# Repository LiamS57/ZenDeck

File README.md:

# ZenDeck

<h3 align="center">
This is a hard-fork of CNCDan's fantastic ZenDeck project, which incorporates a Ryzen-powered Mini-PC into a custom-built handheld gaming console!
</h3>

## Acknowledgement

The majority of this work is based on the previous work of CNCDan (see the upstream repo!). As such, my adjustments would not have been possible without many months of development on his end. If you find that this work benefits you or inspires you to make your own ZenDeck, please take a look at his original project -- as well as his other works -- and show him your support!

**CNCDan's Youtube:**
https://www.youtube.com/@cncdan

**CNCDan's Original ZenDeck Development Log:**
https://www.youtube.com/watch?v=_ST59qbFj8Q&list=PLy9j9_dmmg2TrMOIG65j3nOELqgDXPkkn

## Info

This repository intends to serve as a build diary and general knowledge-base for my specific implementation of the ZenDeck, in the hopes that the details of my attempt are helpful to others interested in constructing one.
I had started my implementation a few months before forking the repository, so some details are not part of the commit history; however, **there is still quite a bit to finish**, and future changes/updates will be recorded here.

Please note that this is not a one-to-one recreation -- I have made several design changes to better suit my use-case. The major points are provided in this readme, but smaller changes are described in more detail in each directory.

## Features

- Customizable mounting system for other Mini-PCs
- 8" 1280x800 60hz IPS display (with touch)
- Full-sized Hall effect Joysticks
- Hall effect Triggers
- Full-sized rumble motors *[IN PROGRESS]*
- IMU/Gyroscopic aim-assist *[IN PROGRESS]*
- Custom USB HID-based controller using LUFA
- Trackpad
- Room for up to 88.8Wh battery capacity (using 6000mah 21700 cells).
- USB-C Charging, power path management and OS integration over USB for battery capacity reporting

## Major Design Changes

The following is a (non-exhaustive) list of high-level design changes I've made from the original design. For more information on smaller details changed, please see the individual section readmes and the commit log.
- Mini-PC: Beelink SER5 Max L (Ryzen 7 6800H, 32GB RAM)
- 2-microcontroller control design instead of 3
  <!-- - To conserve on cost and complexity, I have opted to remove the RHS microcontroller in favor of completely running the controller inputs off of a single Atmega32u4. This also allows me to fit all PCB uC USB connections on a single HS8836A for on-the-go reprogramability. -->
- Pure AVR C instead of Arduino.h
- Higher power BMS (19V, 5A) *[IN PROGRESS]*
- Replacement of the TRRS port with an I2C bus header

## Progress
*[COMING SOON]*

## License

This project is licensed under the **CERN Open Hardware Licence Version 2 – Strongly Reciprocal** (CERN-OHL-S-2.0), similar to and as directed by the upstream repository.
A copy of the full license is available in the [license](Licence) file.

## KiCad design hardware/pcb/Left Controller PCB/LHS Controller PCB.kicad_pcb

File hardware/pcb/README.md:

# PCBs

All PCB files have been edited through KiCad, but it should be trivial to import these into other editors. 

## Design Changes

Most of the actual changes have been made on the LHS/RHS Controller PCBs, but some of the other PCBs have been updated for newer KiCad version.

### Controller PCBs

#### ▶ Microcontroller Count Reduction

In the original RHS Controller, a third AVR microcontroller was used to offload processing for right-hand controls. I have adjusted the design to remove this microcontroller, and all inputs are now redirected back to the LHS Controller via an additional 10-pin FFC connector (J6 in LHS Controller). Likewise, the I2C bus connection on the first 10-pin FFC connector has been removed.

This configuration allows for all microcontrollers in the system to directly connect to the onboard USB hub (HS8836A). In the original design, if there was any need to reprogram the RHS microcontroller, it would have to be done manually through the SPI bus test pads with an in-system programmer; however, if all of them can connect to the hub, then they can all be re-flashed over USB while on the go.

One downside to this design is that it requires literally *every* pin on the gamepad Atmega32u4 to cover the rest of the inputs. The microcontroller is more than capable of handling this, but the ability to add anything else (like new buttons) is severely limited!

> [!WARNING]
In my current redesign, the rumble motors are unfortunately both on pins that use the **same timer** (Timer 4). This means they cannot use different PWM frequencies. I am currently looking into a firmware workaround for this, but if you use these PCB files, it might be helpful to swap the routing for one of the motors with another PWM-capable pin!

> [!NOTE]
In my implementation, I was unable to find an LED package that matched the footprints around the joystick holes. When looking at the LEDs specified in the original KiCad files (APA102), they match physically, but the pin layout is incorrect. I did not replace these and did not try to populate them when I ordered my boards, but the routing to the trackpad microcontroller has not been changed. YMMV!

#### ▶ Headphone Jack &rarr; I2C Header

I rarely use headphones with an aux cable nowadays, so my redesign replaces the headphone jack with a bit more board space and a header (J8 in LHS Controller) for I2C from the gamepad microcontroller. This bus connection can be used for anything, but its primary intended function in my case is to attach an IMU for gyroscopic aim-assist.

### Battery Management System (BMS)

*[COMING SOON]*

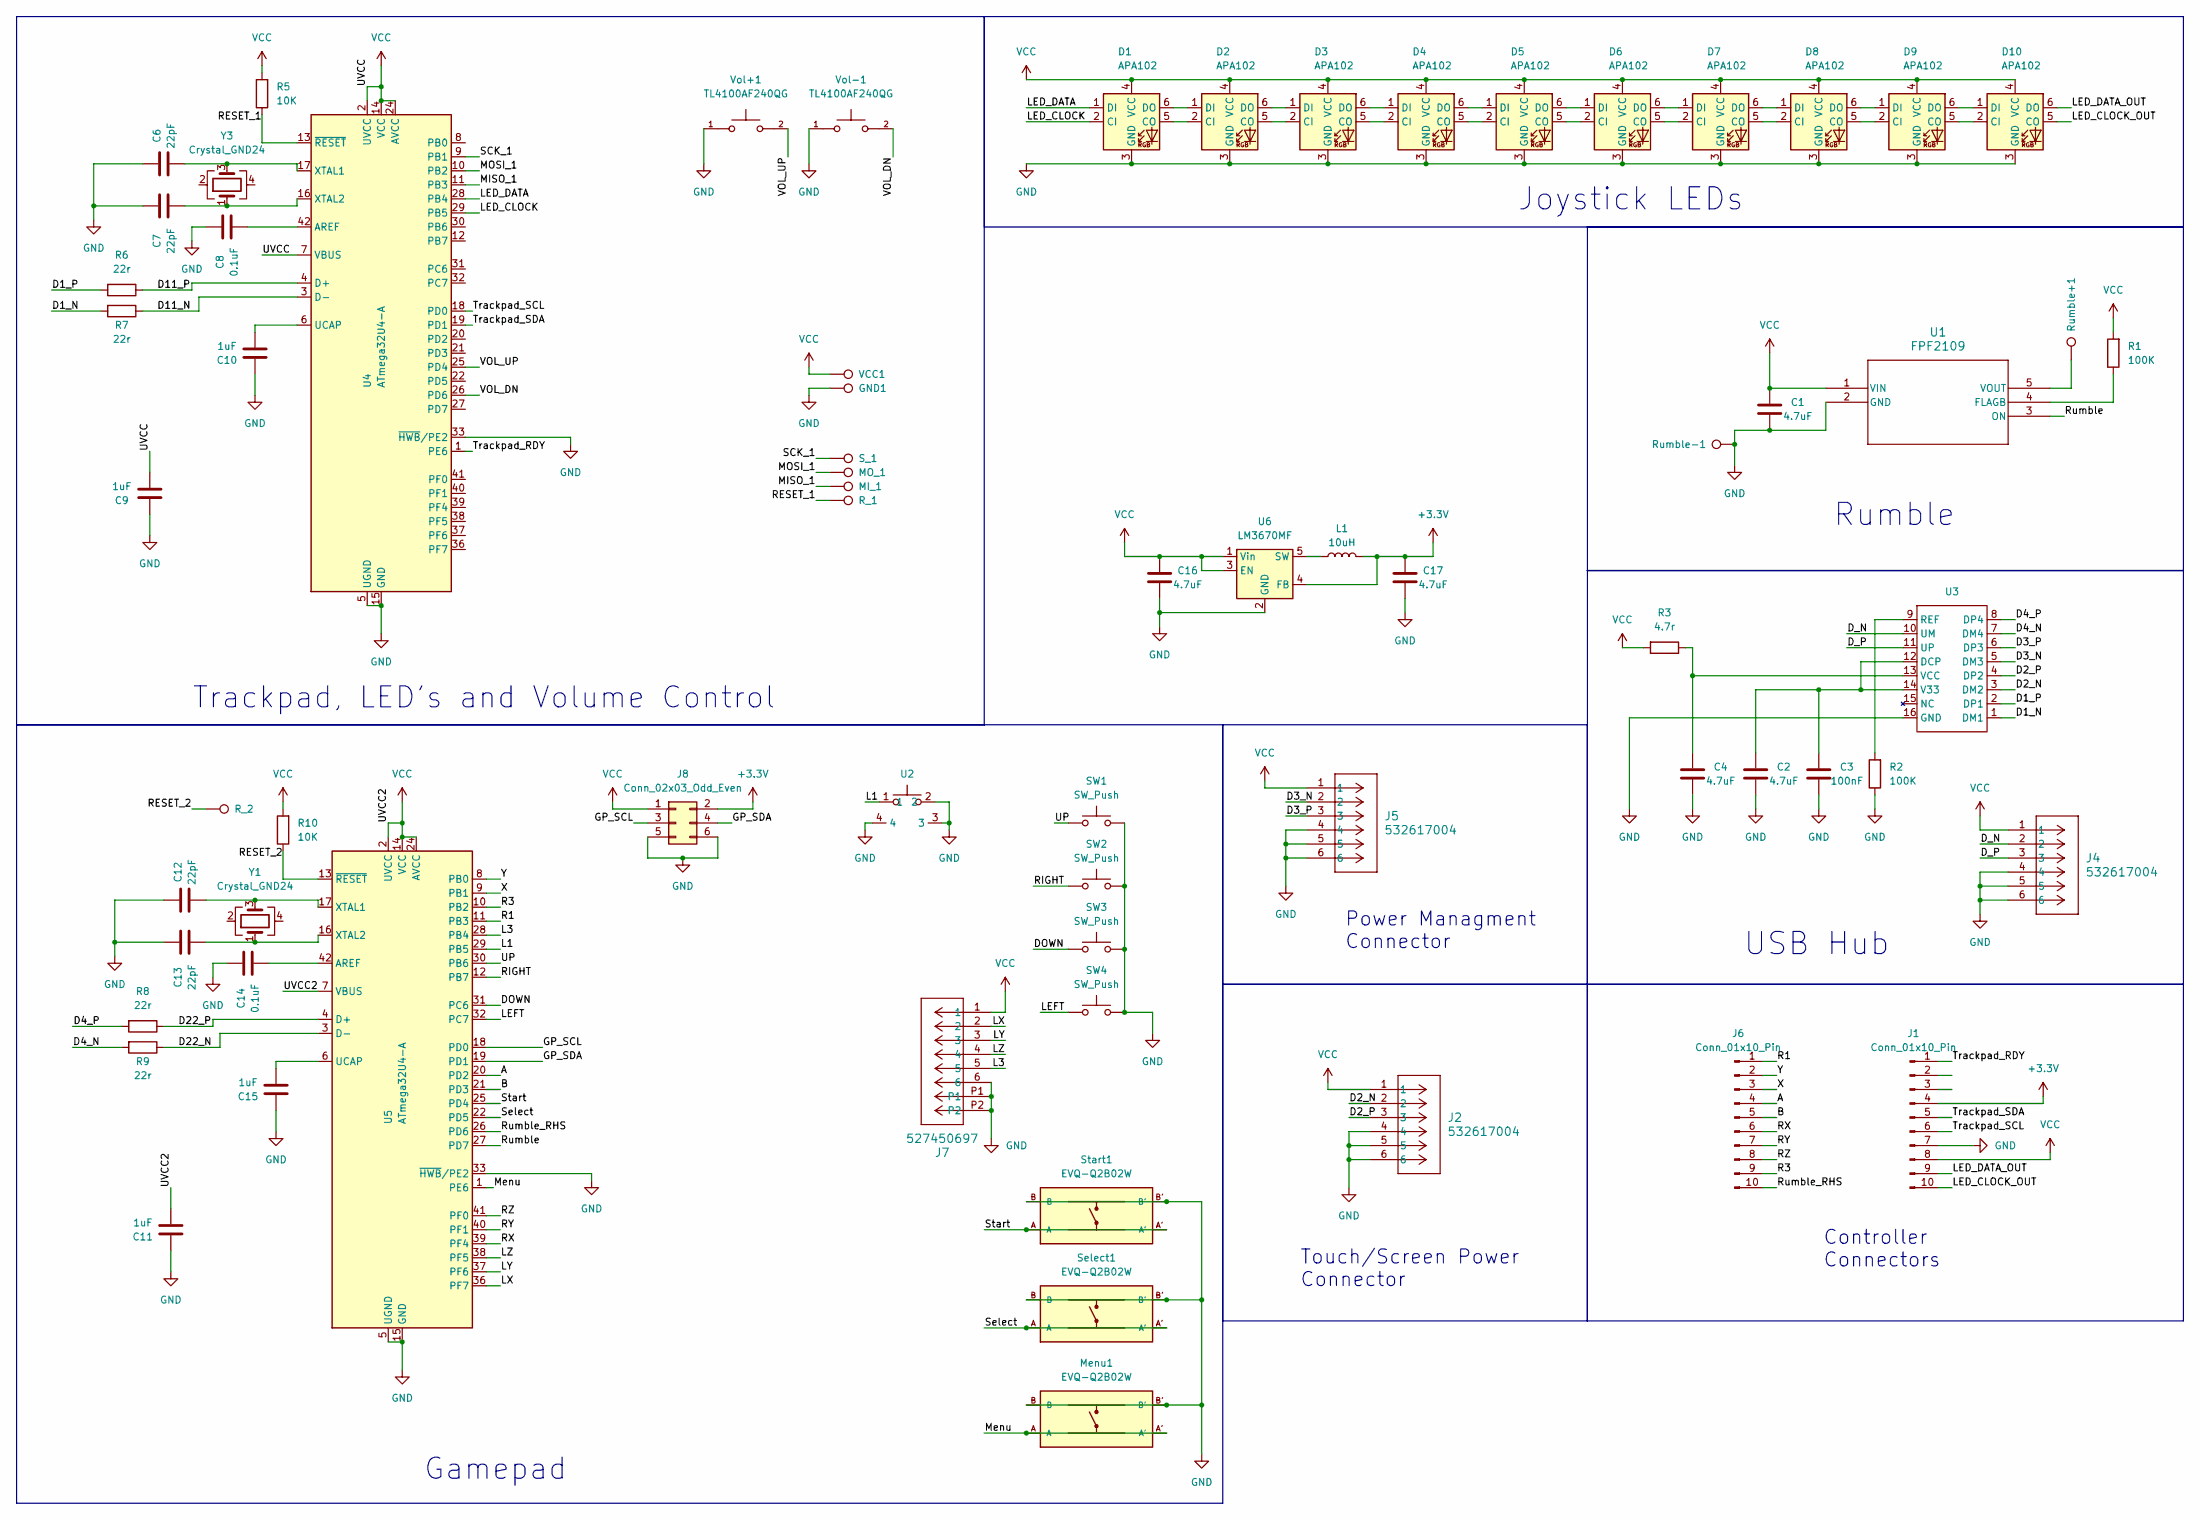
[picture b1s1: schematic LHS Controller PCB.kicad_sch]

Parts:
C1, C2, C4, C16, C17: 4.7uF; C_0603_1608Metric_Pad1.08x0.95mm_HandSolder
C3: 100nF; C_0603_1608Metric_Pad1.08x0.95mm_HandSolder
C6, C7, C12, C13: 22pF; C_0603_1608Metric_Pad1.08x0.95mm_HandSolder
C8, C14: 0.1uF; C_0603_1608Metric_Pad1.08x0.95mm_HandSolder
C9, C10, C11, C15: 1uF; C_0603_1608Metric_Pad1.08x0.95mm_HandSolder
D1, D2, D3, D4, D5, D6, D7, D8, D9, D10: APA102; APA102 2020
GND1: GND; TestPoint_Pad_D1.5mm
J1, J6: Conn_01x10_Pin; TE_1-1734839-0_1x10-1MP_P0.5mm_Horizontal
J2, J4, J5: 532617004; CON_532617004
J7: 527450697; CON_5051100692_MOL
J8: Conn_02x03_Odd_Even; PinHeader_2x03_P2.54mm_Vertical
L1: 10uH; L_Taiyo-Yuden_MD-4040
MI_1: MISO_1; TestPoint_Pad_D1.5mm
MO_1: MOSI_1; TestPoint_Pad_D1.5mm
Menu1: EVQ-Q2B02W; SW_EVQ-Q2B02W
R1, R2: 100K; R_0603_1608Metric_Pad0.98x0.95mm_HandSolder
R3: 4.7r; R_0603_1608Metric_Pad0.98x0.95mm_HandSolder
R5, R10: 10K; R_0603_1608Metric_Pad0.98x0.95mm_HandSolder
R6, R7, R8, R9: 22r; R_0603_1608Metric_Pad0.98x0.95mm_HandSolder
R_1: RESET_1; TestPoint_Pad_D1.5mm
R_2: RESET_2; TestPoint_Pad_D1.5mm
Rumble+1: Rumble+; TestPoint_THTPad_D2.0mm_Drill1.0mm
Rumble-1: Rumble-; TestPoint_THTPad_D2.0mm_Drill1.0mm
SW1, SW2, SW3, SW4: SW_Push; Membrane Button Small
S_1: SCK_1; TestPoint_Pad_D1.5mm
Select1: EVQ-Q2B02W; SW_EVQ-Q2B02W
Start1: EVQ-Q2B02W; SW_EVQ-Q2B02W
U1: FPF2109; SOT-23-5
U2: MJTP1117
U3: SOP-16_3.9x9.9mm_P1.27mm
U4, U5: ATmega32U4-A; TQFP-44_10x10mm_P0.8mm
U6: LM3670MF; TSOT-23-5
VCC1: VCC; TestPoint_Pad_D1.5mm
Vol+1: TL4100AF240QG; SW_TL4100AF240QG; PARTREV C
Vol-1: TL4100AF240QG; SW_TL4100AF240QG; PARTREV C
Y1, Y3: Crystal_GND24; Crystal_SMD_5032-4Pin_5.0x3.2mm

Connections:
+3.3V: C17.1, J1.4, J8.2, L1.2, U6.4 (FB)
/A: J6.4, U5.20 (PD2)
/B: J6.5, U5.21 (PD3)
/D1_N: R7.2, U3.1 (DM1)
/D1_P: R6.2, U3.2 (DP1)
/D2_N: J2.2, U3.3 (DM2)
/D2_P: J2.3, U3.4 (DP2)
/D3_N: J5.2, U3.5 (DM3)
/D3_P: J5.3, U3.6 (DP3)
/D4_N: R9.2, U3.7 (DM4)
/D4_P: R8.2, U3.8 (DP4)
/D11_N: R7.1, U4.3 (D-)
/D11_P: R6.1, U4.4 (D+)
/D22_N: R9.1, U5.3 (D-)
/D22_P: R8.1, U5.4 (D+)
/DOWN: SW3.1, U5.31 (PC6)
/D_N: J4.2, U3.10 (UM)
/D_P: J4.3, U3.11 (UP)
/GP_SCL: J8.3, U5.18 (PD0)
/GP_SDA: J8.4, U5.19 (PD1)
/L1: U2.1, U5.29 (PB5)
/L3: J7.5, U5.28 (PB4)
/LED_CLOCK: D1.2 (CI), U4.29 (PB5)
/LED_CLOCK_OUT: D10.5 (CO), J1.10
/LED_DATA: D1.1 (DI), U4.28 (PB4)
/LED_DATA_OUT: D10.6 (DO), J1.9
/LEFT: SW4.1, U5.32 (PC7)
/LX: J7.2, U5.36 (PF7)
/LY: J7.3, U5.37 (PF6)
/LZ: J7.4, U5.38 (PF5)
/MISO_1: MI_1.1, U4.11 (PB3)
/MOSI_1: MO_1.1, U4.10 (PB2)
/Menu: Menu1.A, Menu1.A', U5.1 (PE6)
/R1: J6.1, U5.11 (PB3)
/R3: J6.9, U5.10 (PB2)
/RIGHT: SW2.1, U5.12 (PB7)
/RX: J6.6, U5.39 (PF4)
/RY: J6.7, U5.40 (PF1)
/RZ: J6.8, U5.41 (PF0)
/Rumble: U1.3 (ON), U5.27 (PD7)
/Rumble_RHS: J6.10, U5.26 (PD6)
/SCK_1: S_1.1, U4.9 (PB1)
/Select: Select1.A, Select1.A', U5.22 (PD5)
/Start: Start1.A, Start1.A', U5.25 (PD4)
/Trackpad_RDY: J1.1, U4.1 (PE6)
/Trackpad_SCL: J1.6, U4.18 (PD0)
/Trackpad_SDA: J1.5, U4.19 (PD1)
/UP: SW1.1, U5.30 (PB6)
/VOL_DN: U4.26 (PD6), Vol-1.2
/VOL_UP: U4.25 (PD4), Vol+1.2
/X: J6.3, U5.9 (PB1)
/Y: J6.2, U5.8 (PB0)
GND: C1.2, C2.2, C3.2, C4.2, C6.1, C7.1, C8.1, C9.1, C10.1, C11.1, C12.1, C13.1, C14.1, C15.1, C16.2, C17.2, D1.3 (GND), D2.3 (GND), D3.3 (GND), D4.3 (GND), D5.3 (GND), D6.3 (GND), D7.3 (GND), D8.3 (GND), D9.3 (GND), D10.3 (GND), GND1.1, J1.7, J2.4, J2.5, J2.6, J4.4, J4.5, J4.6, J5.4, J5.5, J5.6, J7.6, J7.P1, J7.P2, J8.5, J8.6, Menu1.B, Menu1.B', R2.1, Rumble-1.1, SW1.2, SW2.2, SW3.2, SW4.2, Select1.B, Select1.B', Start1.B, Start1.B', U1.2 (GND), U2.2, U2.3, U2.4, U3.16 (GND), U4.5 (UGND), U4.15 (GND), U4.23 (GND), U4.33 (~HWB/PE2), U4.35 (GND), U4.43 (GND), U5.5 (UGND), U5.15 (GND), U5.23 (GND), U5.33 (~HWB/PE2), U5.35 (GND), U5.43 (GND), U6.2 (GND), Vol+1.1, Vol-1.1
unnamed: D1.5 (CO), D2.2 (CI)
unnamed: D1.6 (DO), D2.1 (DI)
unnamed: D2.5 (CO), D3.2 (CI)
unnamed: D2.6 (DO), D3.1 (DI)
unnamed: D3.5 (CO), D4.2 (CI)
unnamed: D3.6 (DO), D4.1 (DI)
unnamed: D4.5 (CO), D5.2 (CI)
unnamed: D4.6 (DO), D5.1 (DI)
unnamed: D5.5 (CO), D6.2 (CI)
unnamed: D5.6 (DO), D6.1 (DI)
unnamed: D6.5 (CO), D7.2 (CI)
unnamed: D6.6 (DO), D7.1 (DI)
unnamed: D7.5 (CO), D8.2 (CI)
unnamed: D7.6 (DO), D8.1 (DI)
unnamed: D8.5 (CO), D9.2 (CI)
unnamed: D8.6 (DO), D9.1 (DI)
unnamed: D9.5 (CO), D10.2 (CI)
unnamed: D9.6 (DO), D10.1 (DI)
unnamed: R1.1, U1.4 (FLAGB)
unnamed: Rumble+1.1, U1.5 (VOUT)
unnamed: C2.1, C3.1, U3.12 (DCP), U3.14 (V33)
unnamed: R2.2, U3.9 (REF)
unnamed: C4.1, R3.1, U3.13 (VCC)
unnamed: C8.2, U4.42 (AREF)
unnamed: C10.2, U4.6 (UCAP)
unnamed: C6.2, U4.17 (XTAL1), Y3.3
unnamed: C7.2, U4.16 (XTAL2), Y3.1
unnamed: C14.2, U5.42 (AREF)
unnamed: C15.2, U5.6 (UCAP)
unnamed: C12.2, U5.17 (XTAL1), Y1.3
unnamed: C13.2, U5.16 (XTAL2), Y1.1
unnamed: L1.1, U6.5 (SW)

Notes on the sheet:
Controller Connectors
Gamepad
Power Managment Connector
USB Hub
Touch/Screen Power Connector
Rumble
Trackpad, LED's and Volume Control
Joystick LEDs

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
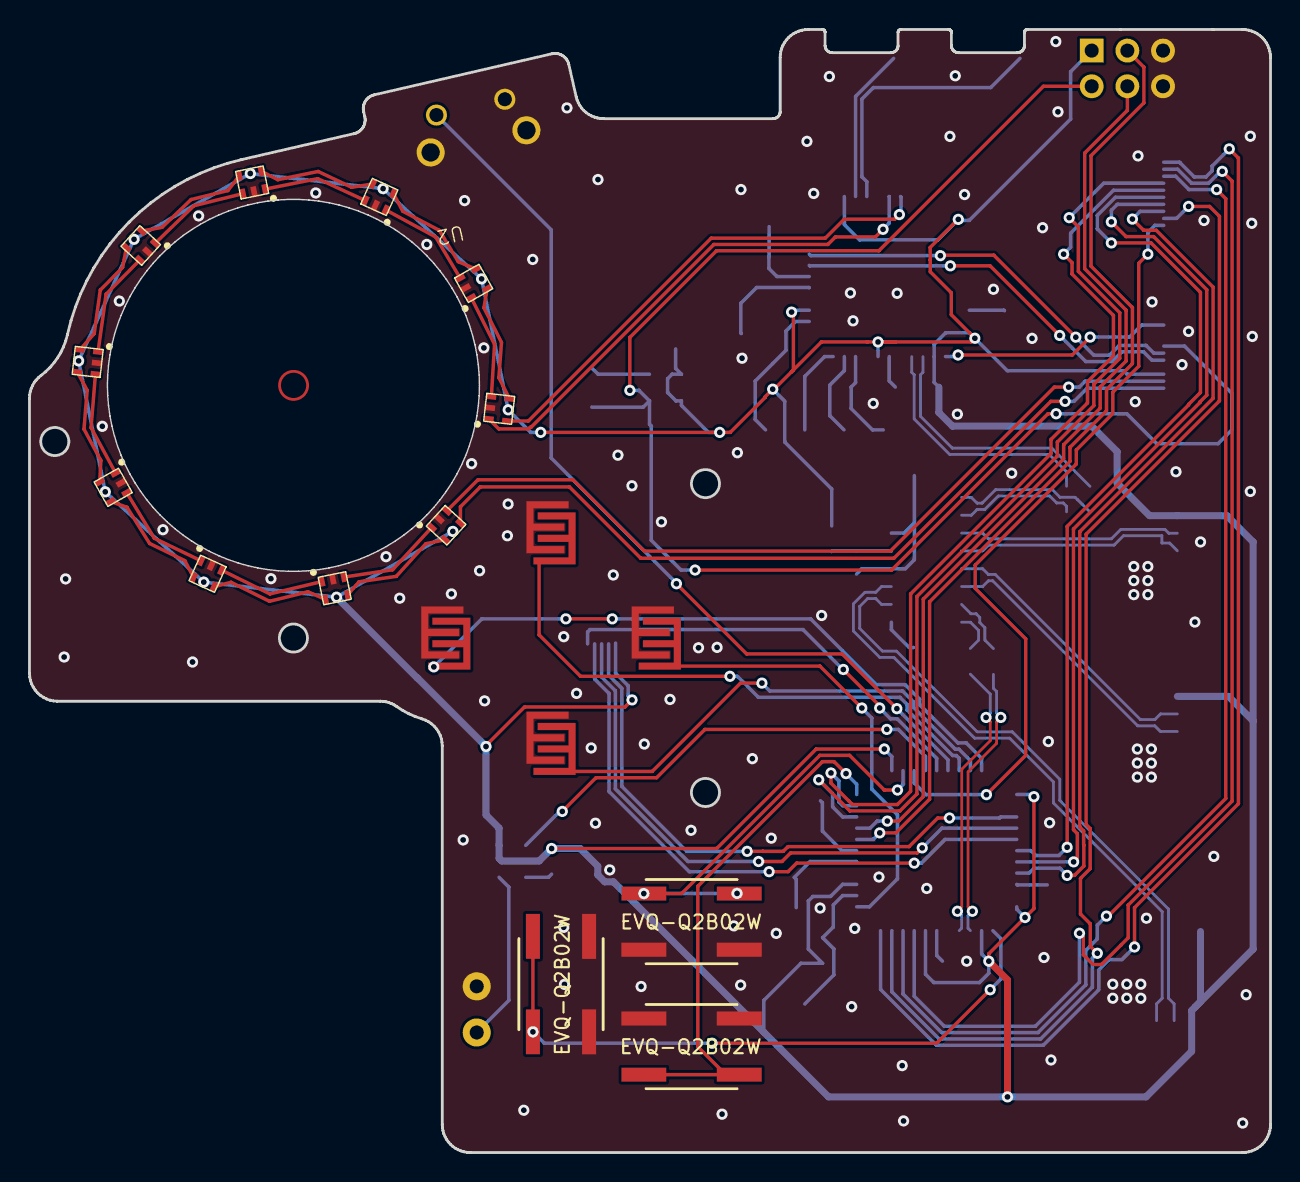
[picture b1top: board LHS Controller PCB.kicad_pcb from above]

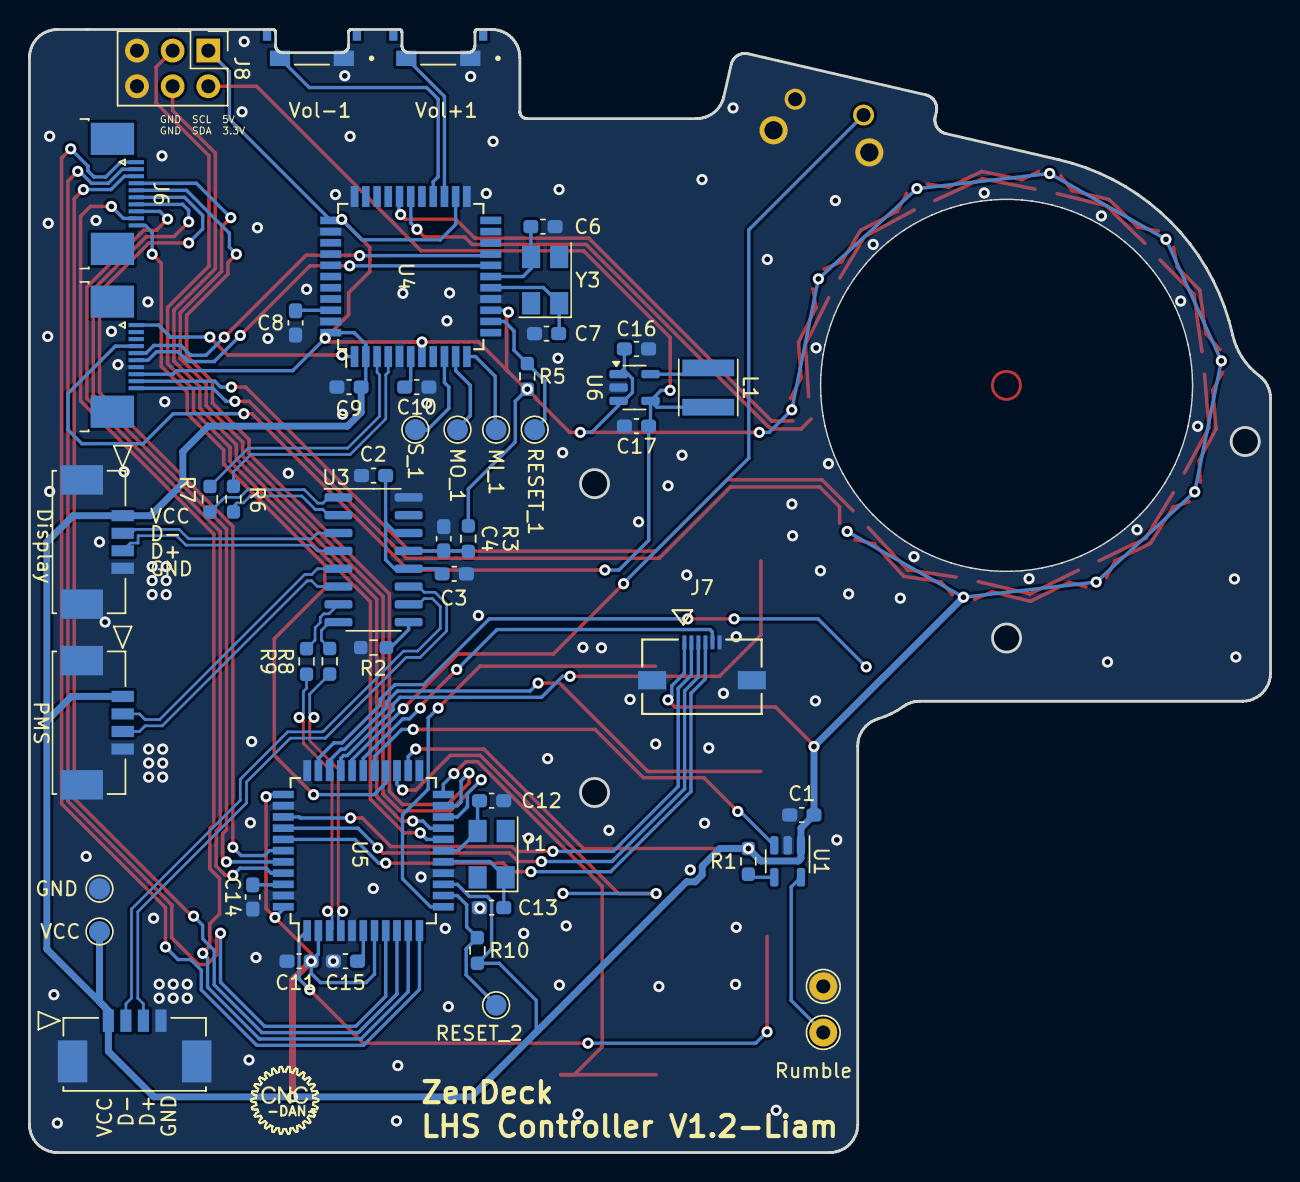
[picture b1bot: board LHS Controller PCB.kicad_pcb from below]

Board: 2 copper layers, 88.4 x 80.0 mm, 69 parts (51 on the bottom side), 88 nets.

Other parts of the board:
RESET_1: RESET_1; TestPoint_Pad_D1.5mm
RESET_2: RESET_2; TestPoint_Pad_D1.5mm

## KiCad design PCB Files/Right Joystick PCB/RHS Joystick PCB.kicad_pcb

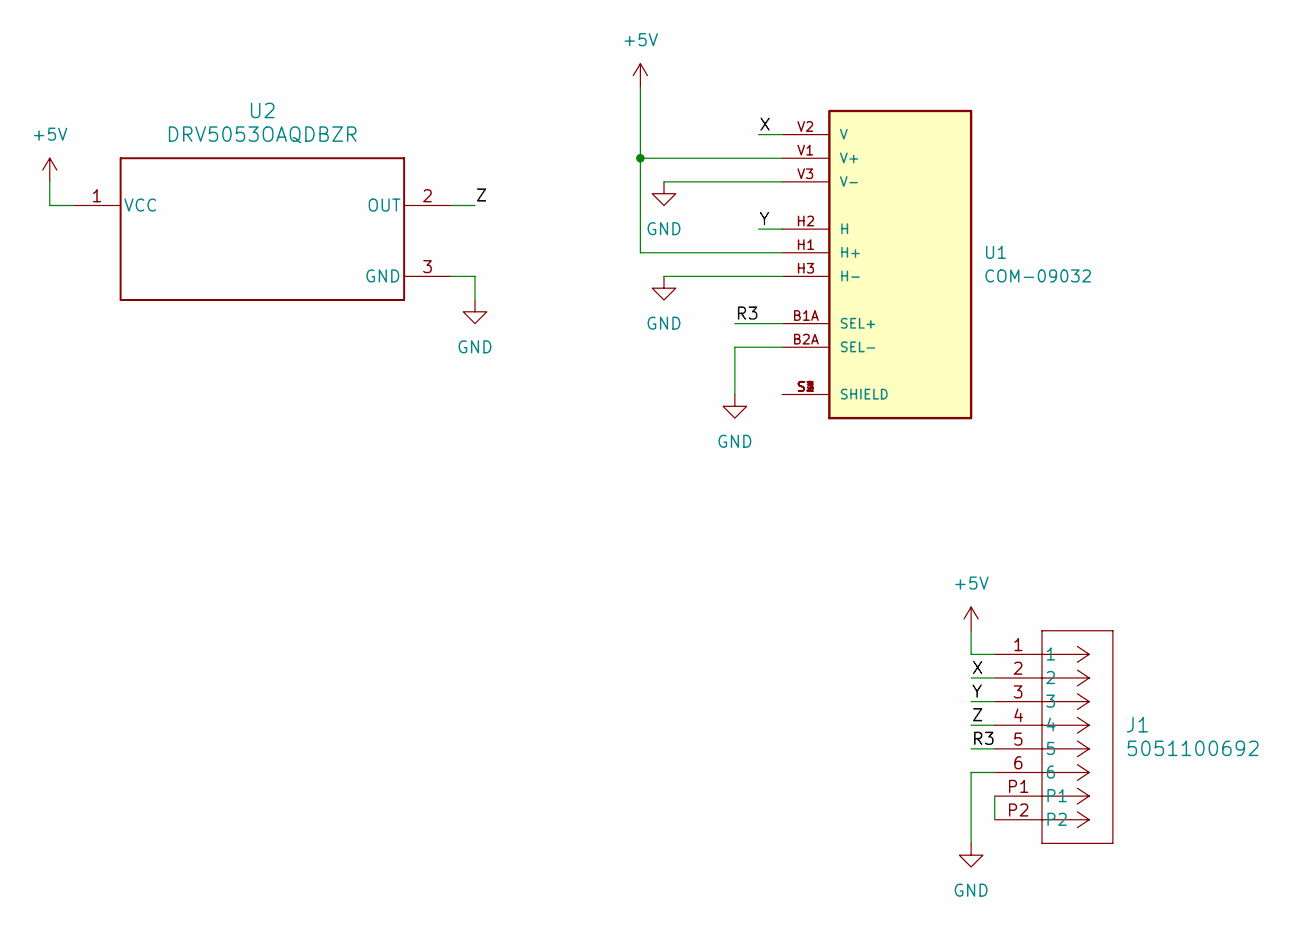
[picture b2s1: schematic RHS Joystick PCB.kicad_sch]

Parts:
J1: 5051100692; CON_5051100692_MOL
U1: COM-09032; PS5 Joystick; PARTREV N/A
U2: DRV5053OAQDBZR; DBZ0003A_N

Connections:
+5V: J1.1, U1.H1 (H+), U1.V1 (V+), U2.1 (VCC)
/R3: J1.5, U1.B1A (SEL+)
/X: J1.2, U1.V2 (V)
/Y: J1.3, U1.H2 (H)
/Z: J1.4, U2.2 (OUT)
GND: J1.6, U1.B2A (SEL-), U1.H3 (H-), U1.V3 (V-), U2.3 (GND)
unnamed: J1.P1, J1.P2
unnamed: U1.S1 (SHIELD), U1.S2 (SHIELD), U1.S3 (SHIELD), U1.S4 (SHIELD)

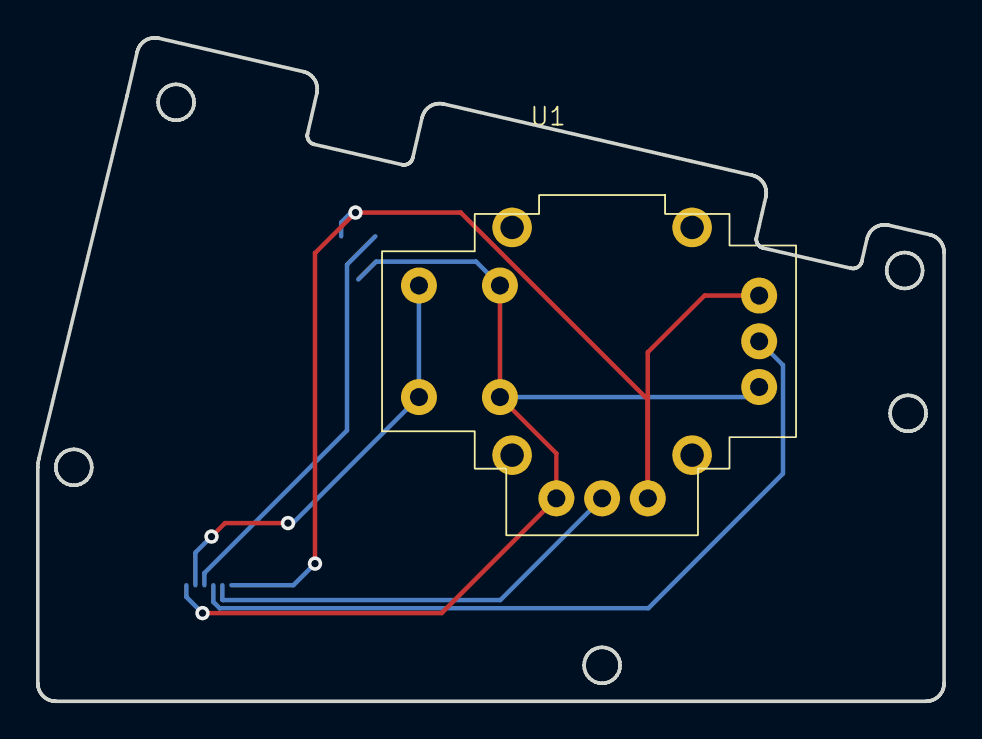
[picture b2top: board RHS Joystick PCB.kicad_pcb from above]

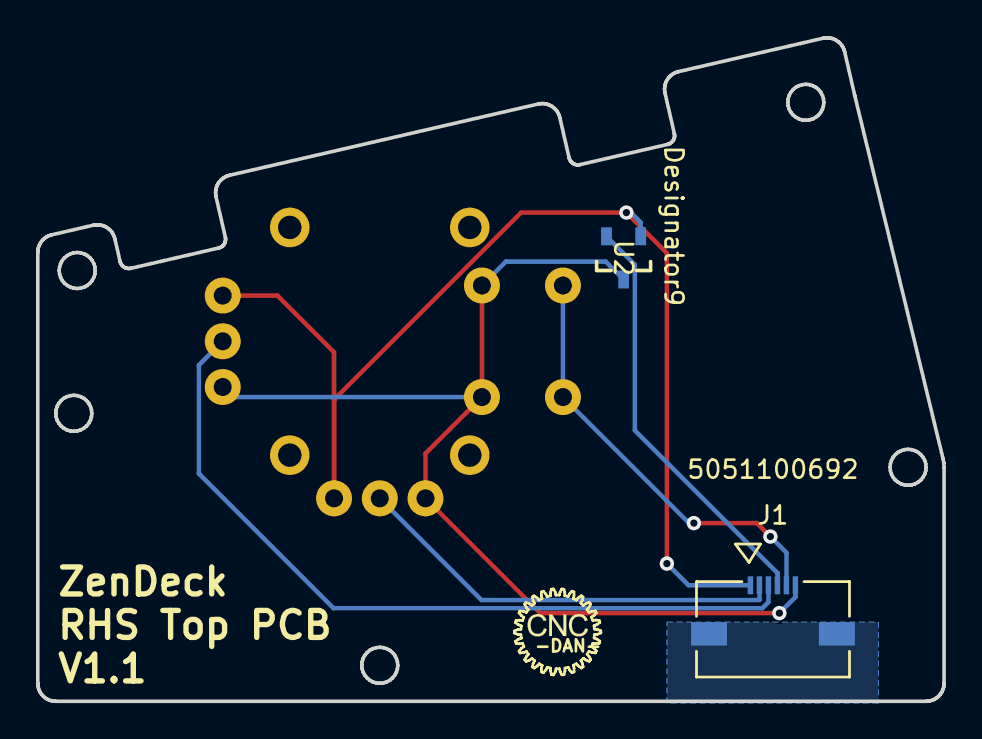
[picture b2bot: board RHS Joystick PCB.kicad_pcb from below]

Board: 2 copper layers, 50.3 x 36.9 mm, 3 parts (2 on the bottom side), 8 nets.

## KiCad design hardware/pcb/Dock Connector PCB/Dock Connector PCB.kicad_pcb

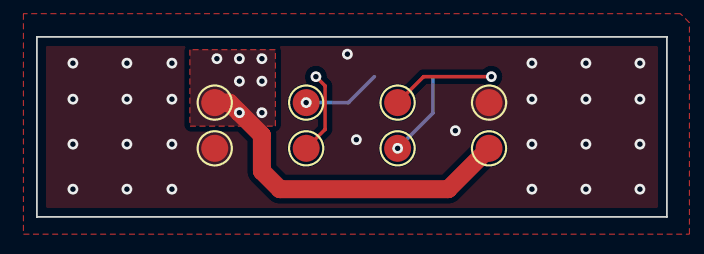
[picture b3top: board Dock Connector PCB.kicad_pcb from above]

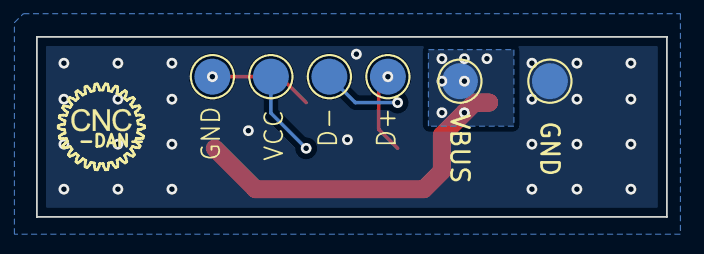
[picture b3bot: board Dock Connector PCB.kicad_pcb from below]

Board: 2 copper layers, 35.0 x 10.0 mm, 14 parts (6 on the bottom side), 6 nets.

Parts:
D3+1: D3+; TestPoint_Pad_D2.0mm
D3-1: D3-; TestPoint_Pad_D2.0mm
D3_N1: D3-; TestPoint_Pad_D1.5mm
D3_P1: D3+; TestPoint_Pad_D1.5mm
GND1, GND2: GND; TestPoint_Pad_D2.0mm
GND3, GND4, GND5: GND; TestPoint_Pad_D1.5mm
VBUS1, VBUS2: VBUS; TestPoint_Pad_D1.5mm
VBUS3: VBUS; TestPoint_Pad_D2.0mm
VCC1: VCC; TestPoint_Pad_D1.5mm
VCC2: VCC; TestPoint_Pad_D2.0mm

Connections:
/D3_N: D3-1.1, D3_N1.1
/D3_P: D3+1.1, D3_P1.1
GND: GND2.1, GND4.1, GND5.1
unnamed: GND1.1, GND3.1
unnamed: VCC1.1, VCC2.1
VBUS: VBUS1.1, VBUS2.1, VBUS3.1

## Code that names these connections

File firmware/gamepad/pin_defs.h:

#ifndef _PIN_DEFS_H_
#define _PIN_DEFS_H_

#include <avr/io.h>

#define BUTTON_X PB1 //X
#define BUTTON_Y PB0 //Y
#define BUTTON_A PD2 //A
#define BUTTON_B PD3 //B

#define BUTTON_L1 PB5 //L1
#define BUTTON_R1 PB3 //R1

#define JOY_L_X PF7 //LX
#define JOY_L_Y PF6 //LY
#define JOY_L_PRESS PB4 //L3

#define JOY_R_X PF4 //RX
#define JOY_R_Y PF1 //RY
#define JOY_R_PRESS PB2 //R3

#define DPAD_U PB6 //UP
#define DPAD_D PC6 //DOWN
#define DPAD_L PC7 //LEFT
#define DPAD_R PB7 //RIGHT

#define BUTTON_MENU PE6 //Menu
#define BUTTON_START PD4 //Start
#define BUTTON_SELECT PD5 //Select

#define TRIGGER_L PF5 //LZ
#define TRIGGER_R PF0 //RZ

#define RUMBLE_L PD7 //Rumble
#define RUMBLE_R PD6 //Rumble_RHS

#endif

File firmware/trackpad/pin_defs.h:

#ifndef _PIN_DEFS_H_
#define _PIN_DEFS_H_

#include <avr/io.h>

#define TRACKPAD_SDA PD1
#define TRACKPAD_SCL PD0
#define TRACKPAD_READY PE6
#define TRACKPAD_I2C_ADDR 0x74

// swapped volume buttons due to interface on Bazzite
#define VOL_PLUS PD6
#define VOL_MINUS PD4

#endif

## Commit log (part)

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2024-12-30 Create Licence
2024-12-30 Add PCB Files, Update Readme
2025-06-22 Added 3D files
2025-06-22 Add full .STEP Assembly
2025-07-18 Added trackpad software
